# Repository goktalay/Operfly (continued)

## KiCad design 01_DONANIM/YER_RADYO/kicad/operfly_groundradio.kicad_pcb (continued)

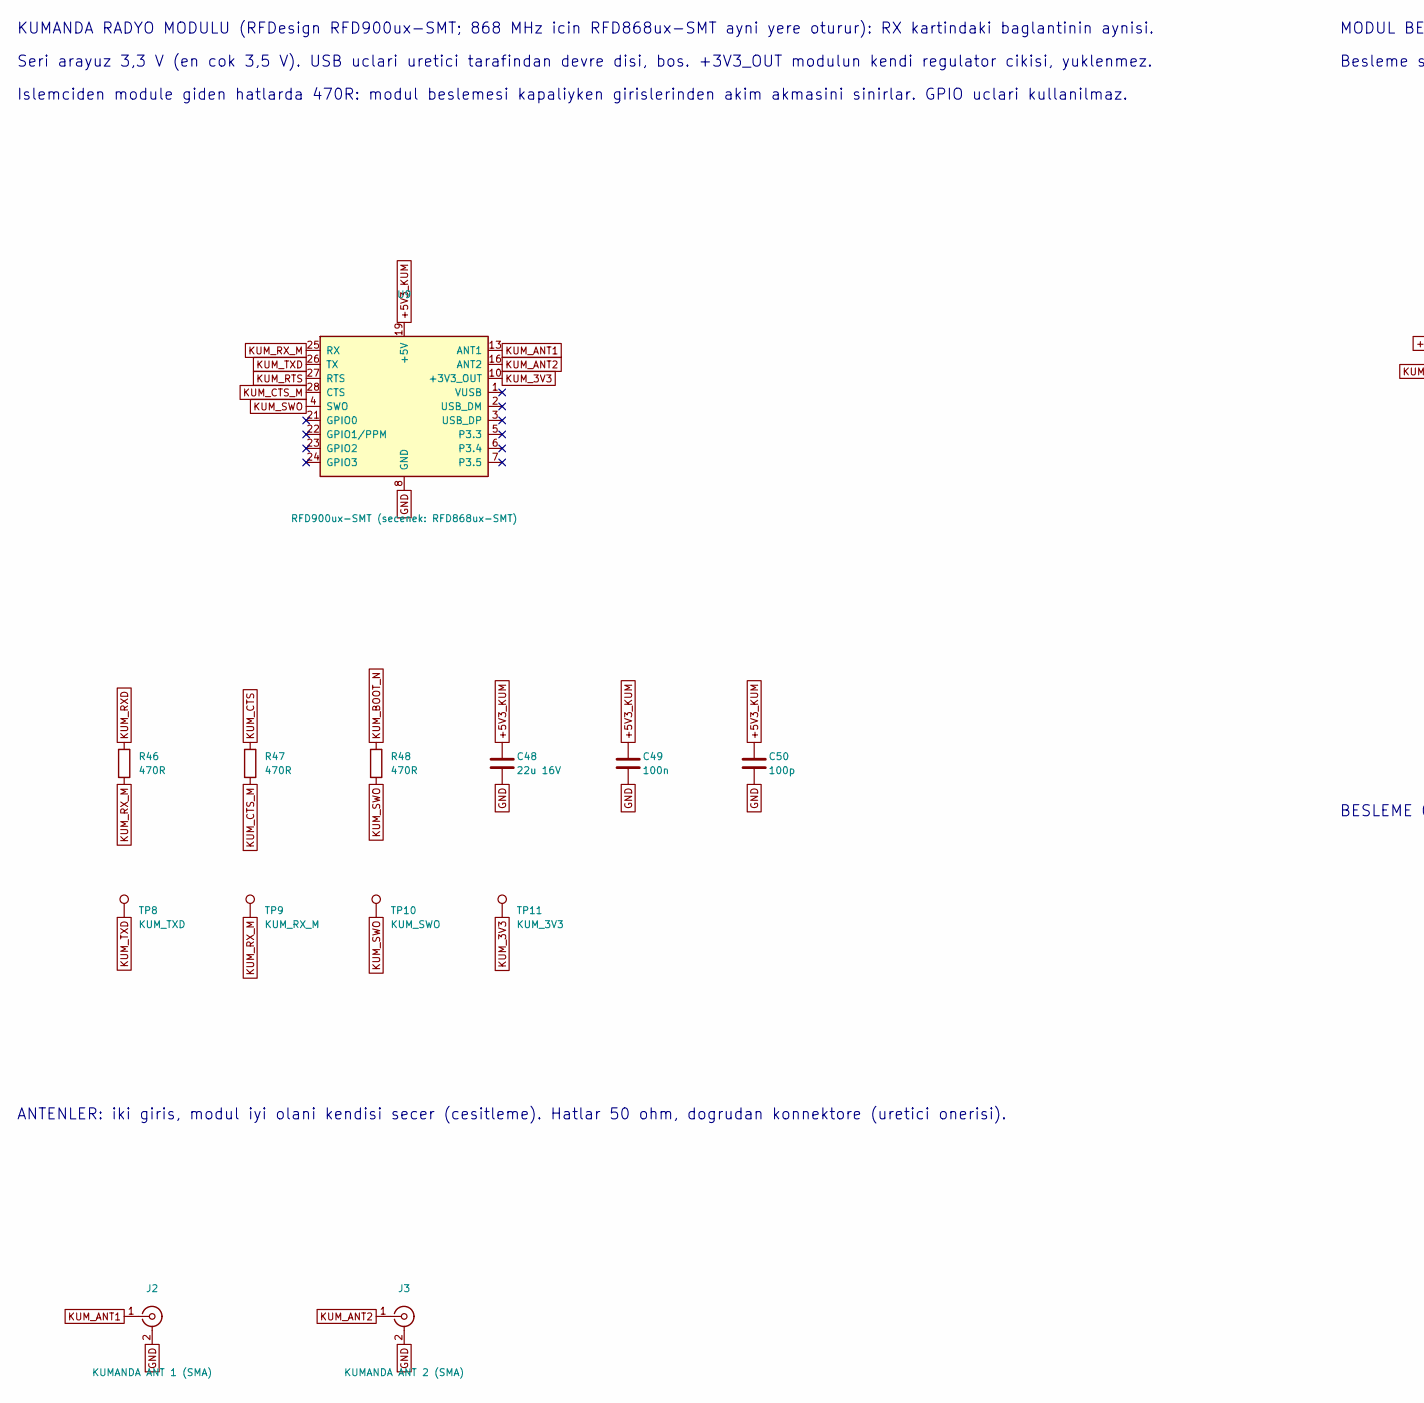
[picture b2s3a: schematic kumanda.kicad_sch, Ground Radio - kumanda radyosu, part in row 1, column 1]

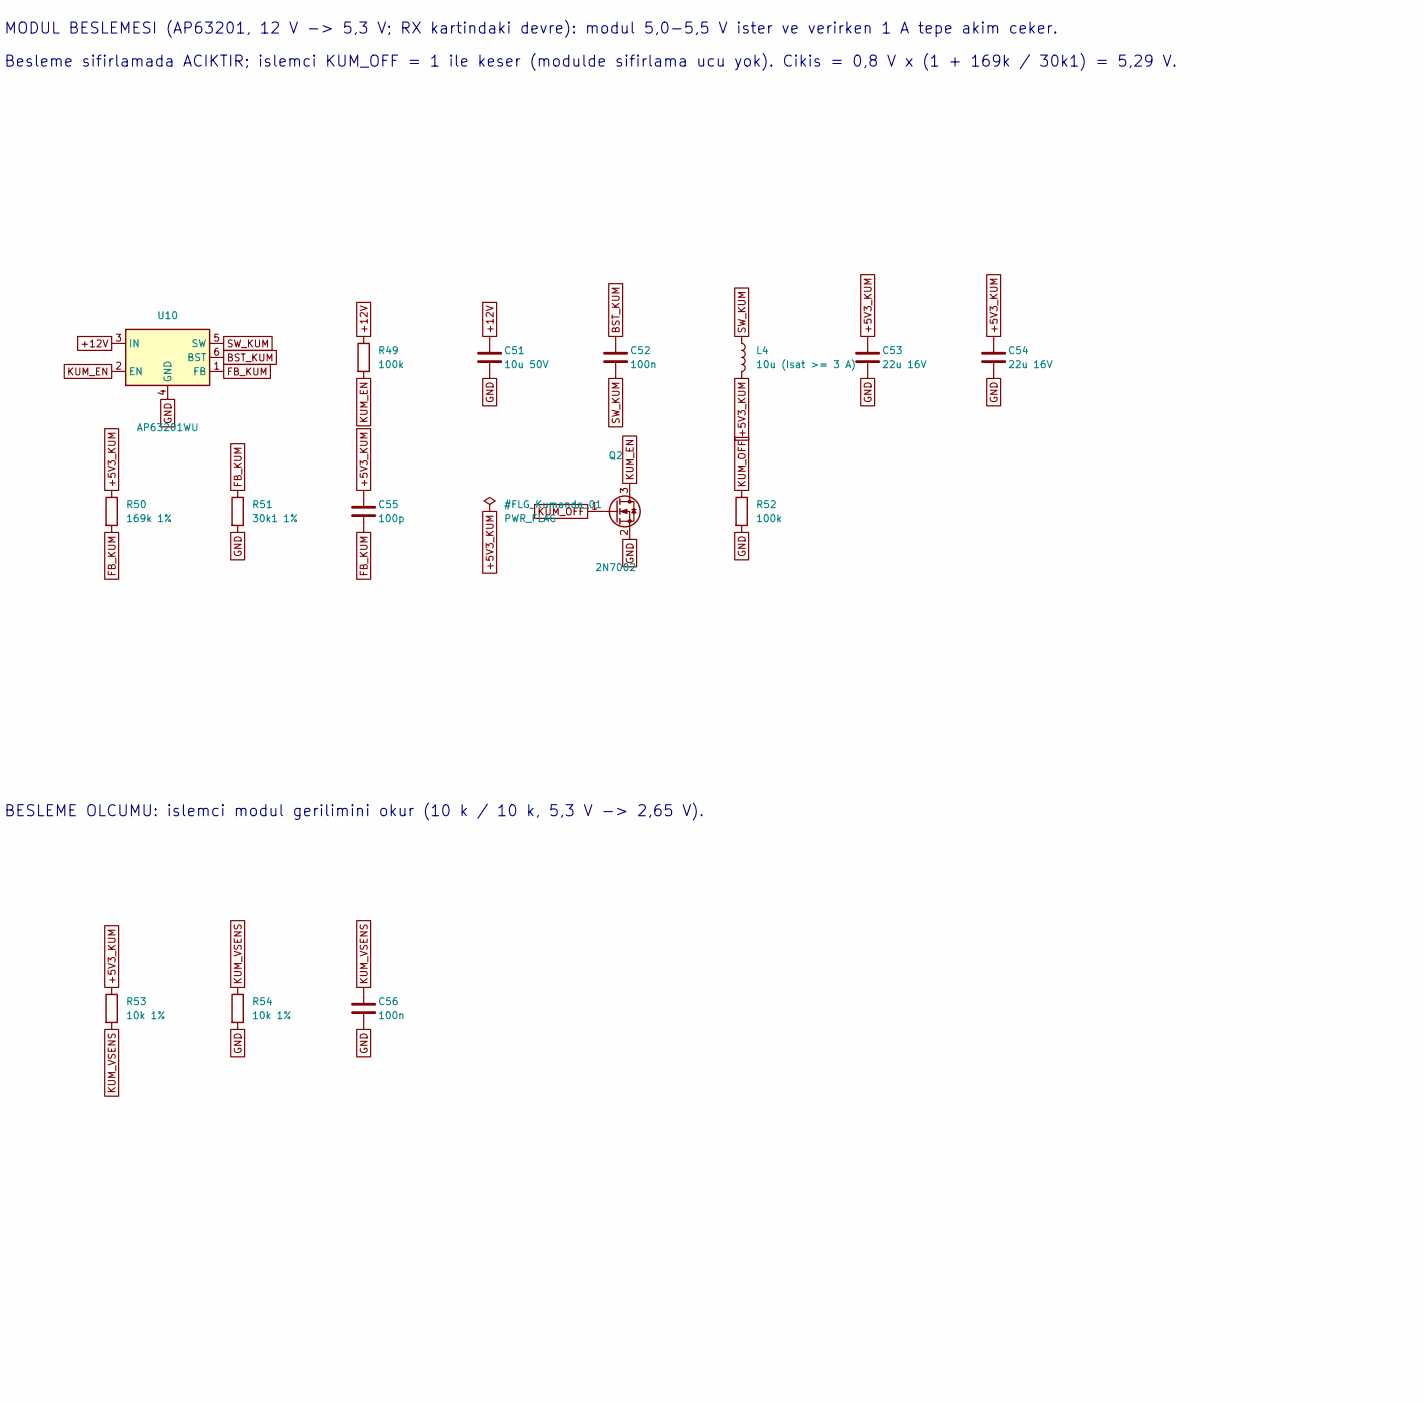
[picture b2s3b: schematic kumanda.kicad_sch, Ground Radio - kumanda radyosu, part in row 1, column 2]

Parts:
C48, C53, C54: 22u 16V; C_1206_3216Metric
C49, C52, C56: 100n; C_0402_1005Metric
C50, C55: 100p; C_0402_1005Metric
C51: 10u 50V; C_1206_3216Metric
J2: KUMANDA ANT 1 (SMA); SMA_Amphenol_132289_EdgeMount
J3: KUMANDA ANT 2 (SMA); SMA_Amphenol_132289_EdgeMount
L4: 10u (Isat >= 3 A); L_Coilcraft_XAL5030-XXX
Q2: 2N7002; SOT-23
R46, R47, R48: 470R; R_0402_1005Metric
R49, R52: 100k; R_0402_1005Metric
R50: 169k 1%; R_0402_1005Metric
R51: 30k1 1%; R_0402_1005Metric
R53, R54: 10k 1%; R_0402_1005Metric
TP8: KUM_TXD; TestPoint_Pad_D1.0mm
TP9: KUM_RX_M; TestPoint_Pad_D1.0mm
TP10: KUM_SWO; TestPoint_Pad_D1.0mm
TP11: KUM_3V3; TestPoint_Pad_D1.0mm
U9: RFD900ux-SMT (secenek: RFD868ux-SMT); RFDesign_RFD900ux-SMT
U10: AP63201WU; TSOT-23-6

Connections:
+5V3_KUM: C48.1, C49.1, C50.1, C53.1, C54.1, C55.1, L4.2, R50.1, R53.1, U9.19 (+5V)
+12V: C51.1, R49.1, U10.3 (IN); also elsewhere on the board
BST_KUM: C52.1, U10.6 (BST)
FB_KUM: C55.2, R50.2, R51.1, U10.1 (FB)
GND: C48.2, C49.2, C50.2, C51.2, C53.2, C54.2, C56.2, J2.2 (Ext), J3.2 (Ext), Q2.2 (S), R51.2, R52.2, R54.2, U9.8 (GND), U9.9 (GND), U9.11 (GND), U9.12 (GND), U9.14 (GND), U9.15 (GND), U9.17 (GND), U9.18 (GND), U9.20 (GND), U9.29 (GND), U9.30 (GND), U10.4 (GND); also elsewhere on the board
KUM_3V3: TP11.1, U9.10 (+3V3_OUT)
KUM_ANT1: J2.1 (In), U9.13 (ANT1)
KUM_ANT2: J3.1 (In), U9.16 (ANT2)
KUM_BOOT_N: R48.1; also elsewhere on the board
KUM_CTS: R47.1; also elsewhere on the board
KUM_CTS_M: R47.2, U9.28 (CTS)
KUM_EN: Q2.3 (D), R49.2, U10.2 (EN)
KUM_OFF: Q2.1 (G), R52.1; also elsewhere on the board
KUM_RTS: U9.27 (RTS); also elsewhere on the board
KUM_RXD: R46.1; also elsewhere on the board
KUM_RX_M: R46.2, TP9.1, U9.25 (RX)
KUM_SWO: R48.2, TP10.1, U9.4 (SWO)
KUM_TXD: TP8.1, U9.26 (TX); also elsewhere on the board
KUM_VSENS: C56.1, R53.2, R54.1; also elsewhere on the board
SW_KUM: C52.2, L4.1, U10.5 (SW)

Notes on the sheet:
Islemciden module giden hatlarda 470R: modul beslemesi kapaliyken girislerinden akim akmasini sinirlar. GPIO uclari kullanilmaz.
BESLEME OLCUMU: islemci modul gerilimini okur (10 k / 10 k, 5,3 V -> 2,65 V).
Seri arayuz 3,3 V (en cok 3,5 V). USB uclari uretici tarafindan devre disi, bos. +3V3_OUT modulun kendi regulator cikisi, yuklenmez.
MODUL BESLEMESI (AP63201, 12 V -> 5,3 V; RX kartindaki devre): modul 5,0-5,5 V ister ve verirken 1 A tepe akim ceker.
Besleme sifirlamada ACIKTIR; islemci KUM_OFF = 1 ile keser (modulde sifirlama ucu yok). Cikis = 0,8 V x (1 + 169k / 30k1) = 5,29 V.
ANTENLER: iki giris, modul iyi olani kendisi secer (cesitleme). Hatlar 50 ohm, dogrudan konnektore (uretici onerisi).
KUMANDA RADYO MODULU (RFDesign RFD900ux-SMT; 868 MHz icin RFD868ux-SMT ayni yere oturur): RX kartindaki baglantinin aynisi.

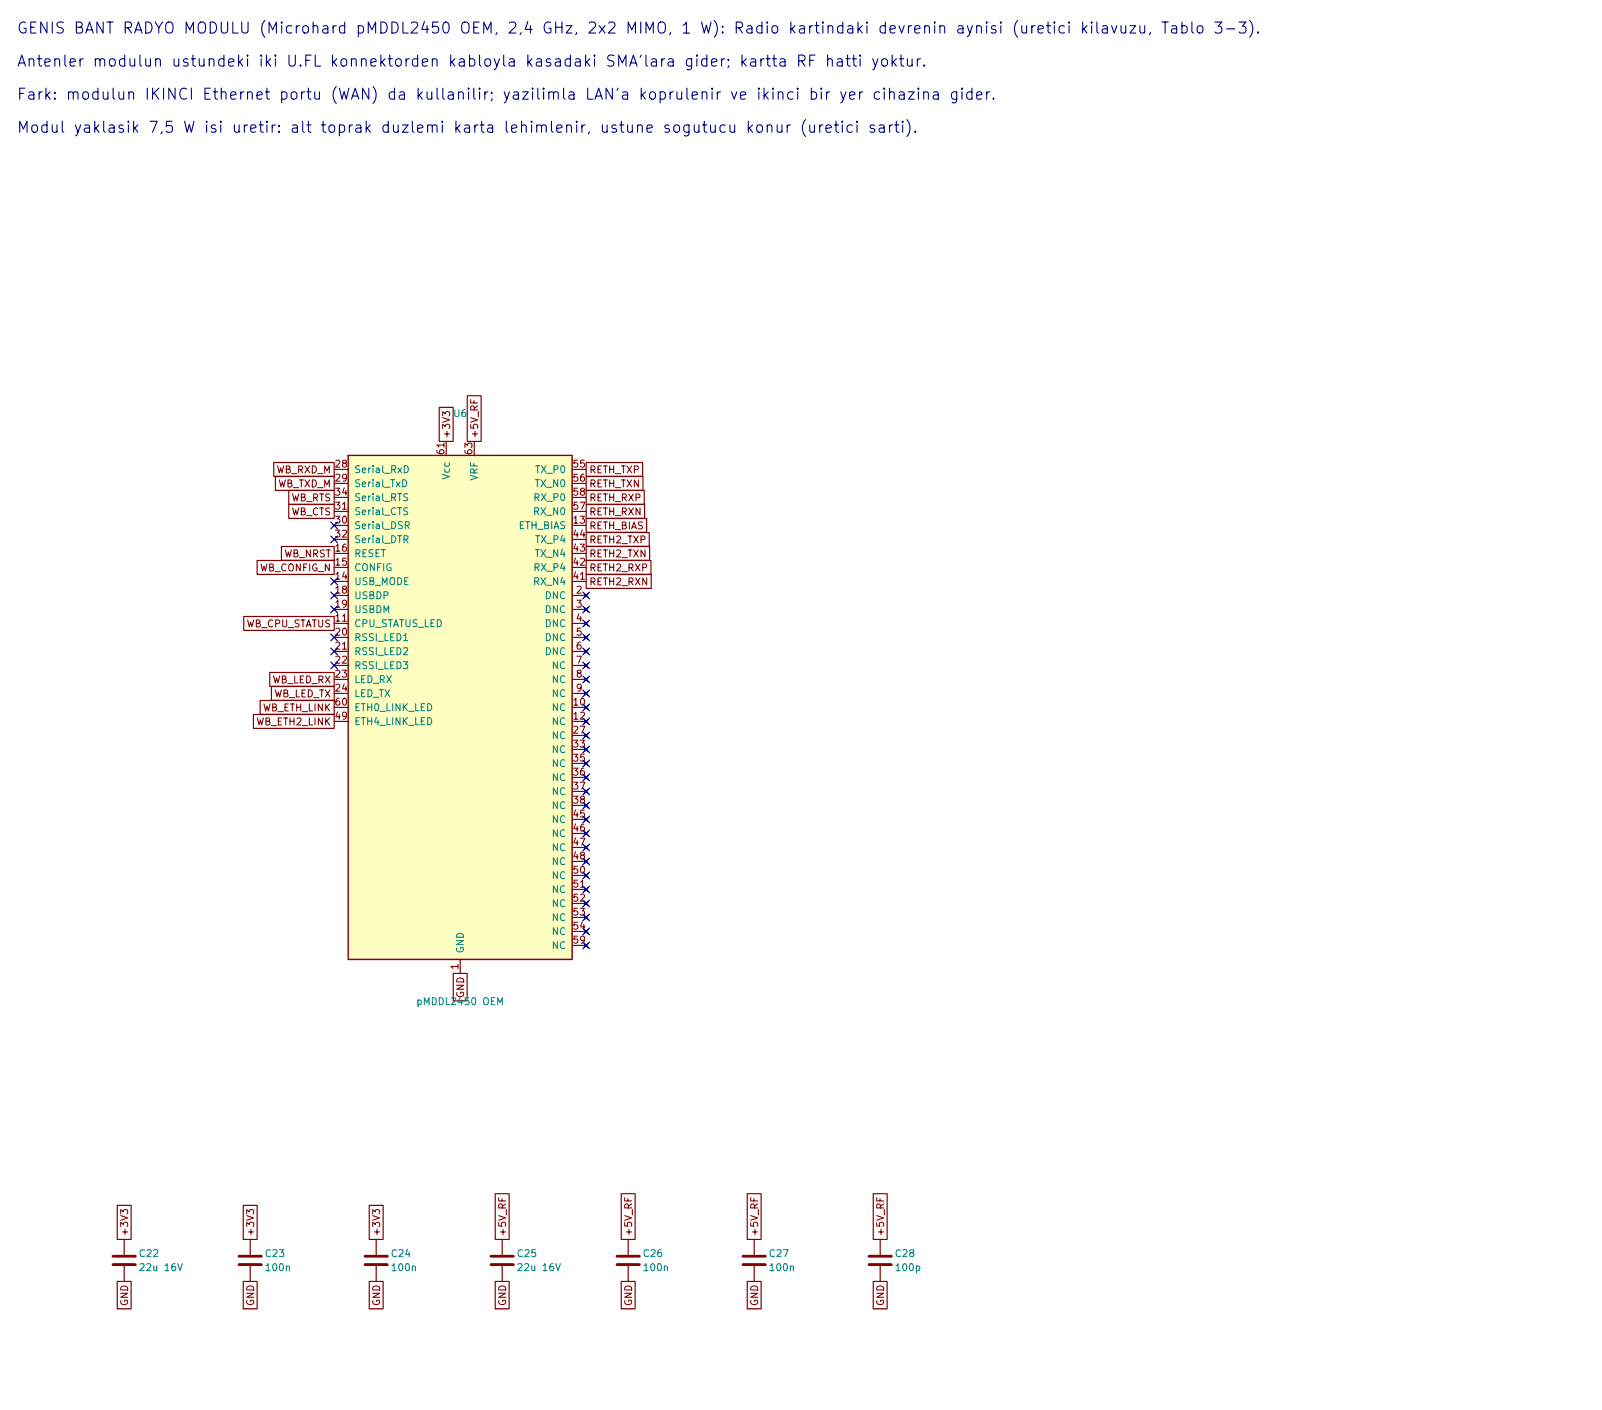
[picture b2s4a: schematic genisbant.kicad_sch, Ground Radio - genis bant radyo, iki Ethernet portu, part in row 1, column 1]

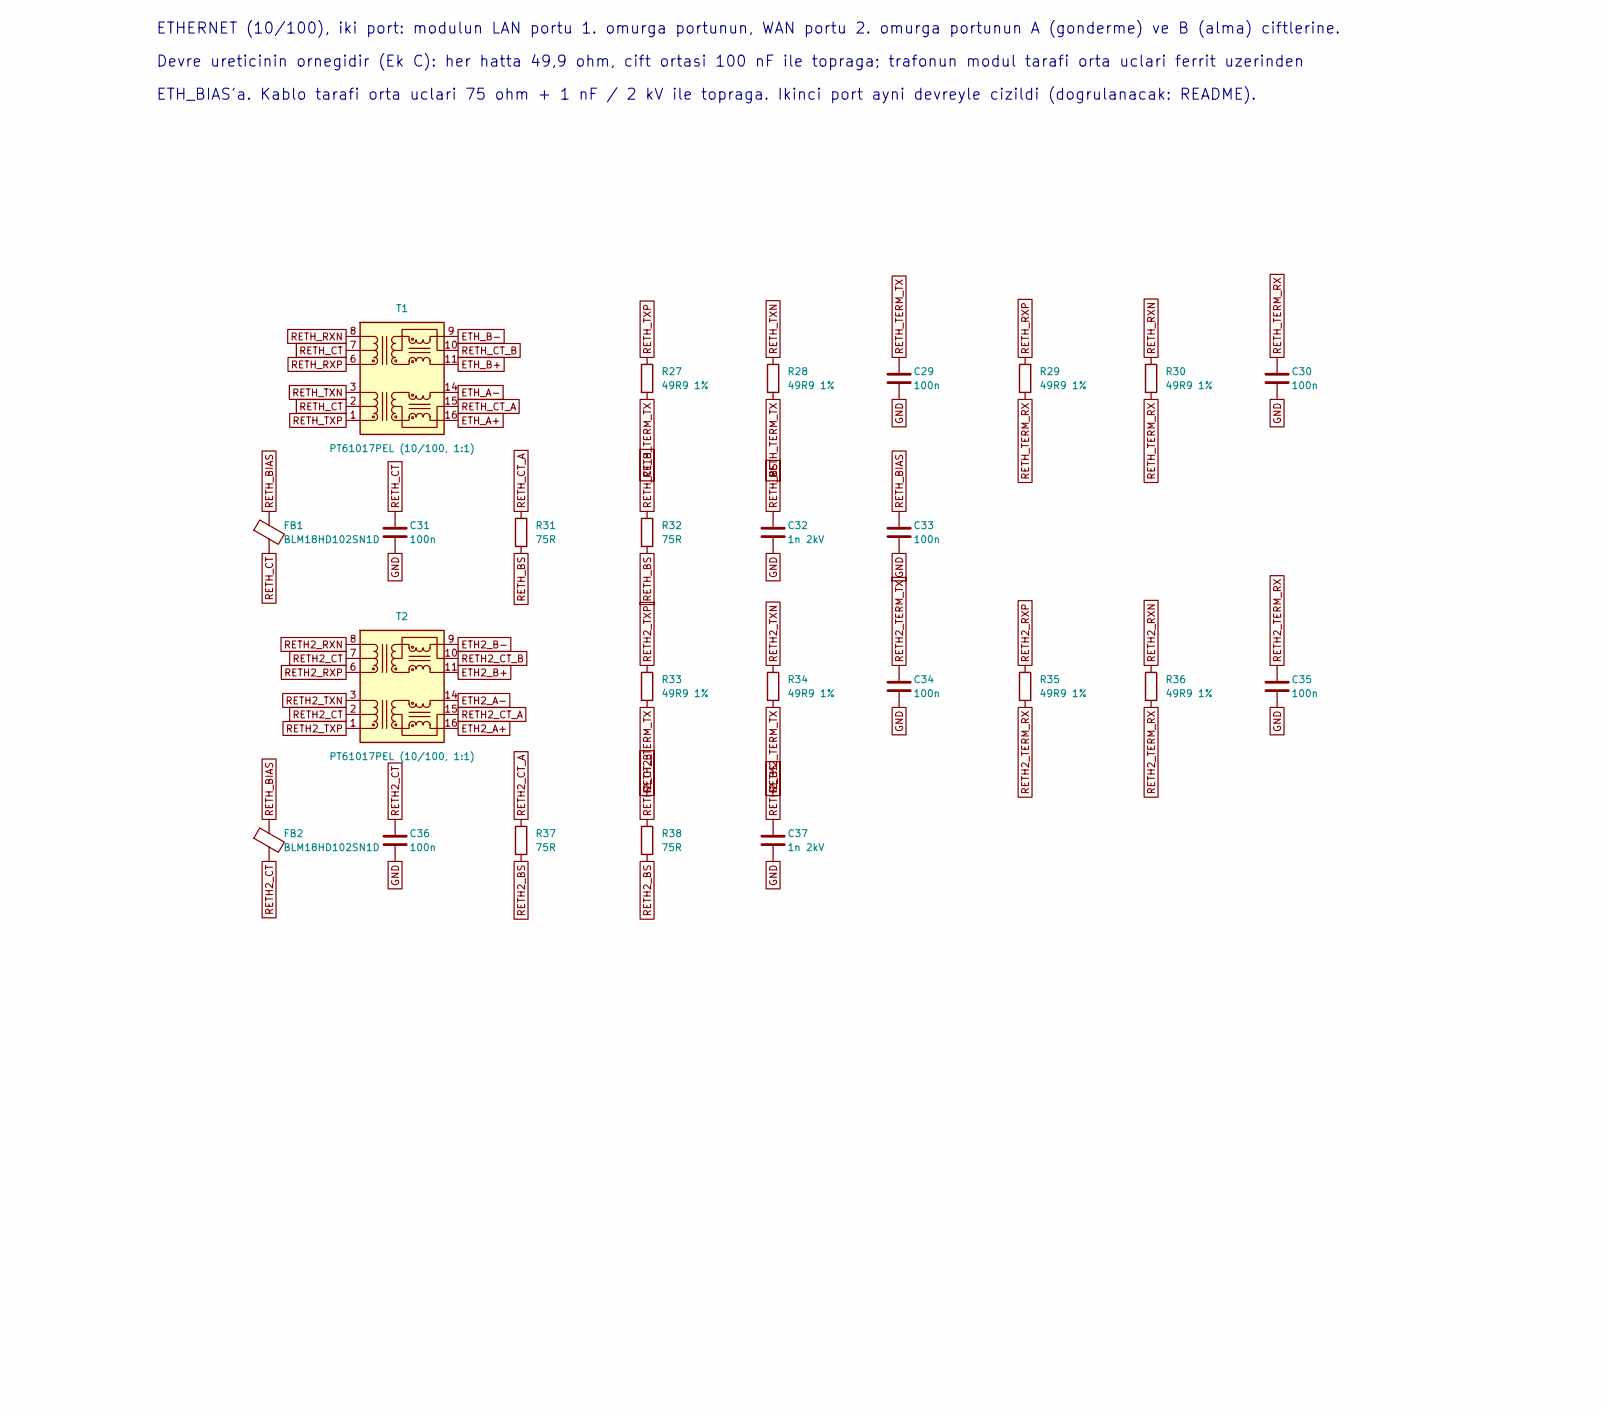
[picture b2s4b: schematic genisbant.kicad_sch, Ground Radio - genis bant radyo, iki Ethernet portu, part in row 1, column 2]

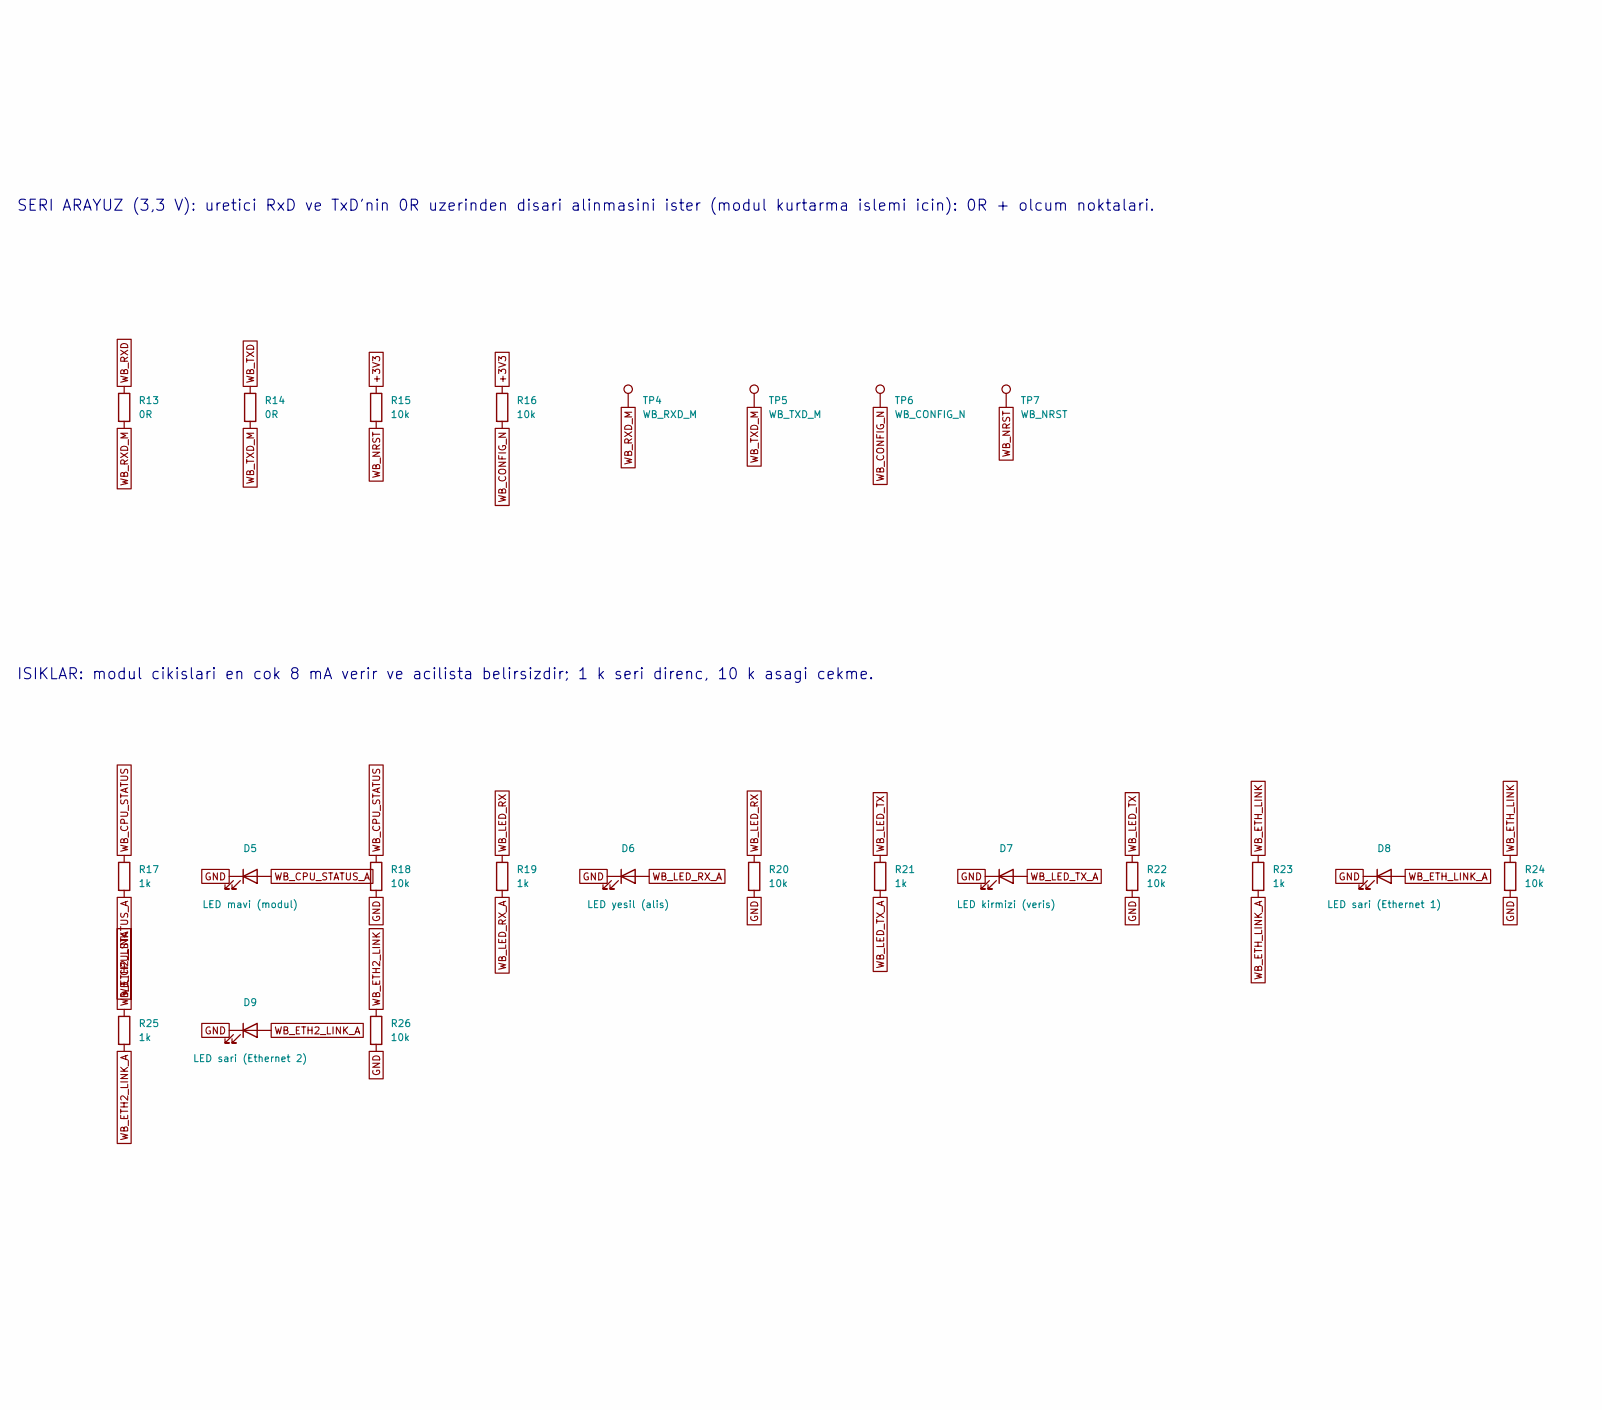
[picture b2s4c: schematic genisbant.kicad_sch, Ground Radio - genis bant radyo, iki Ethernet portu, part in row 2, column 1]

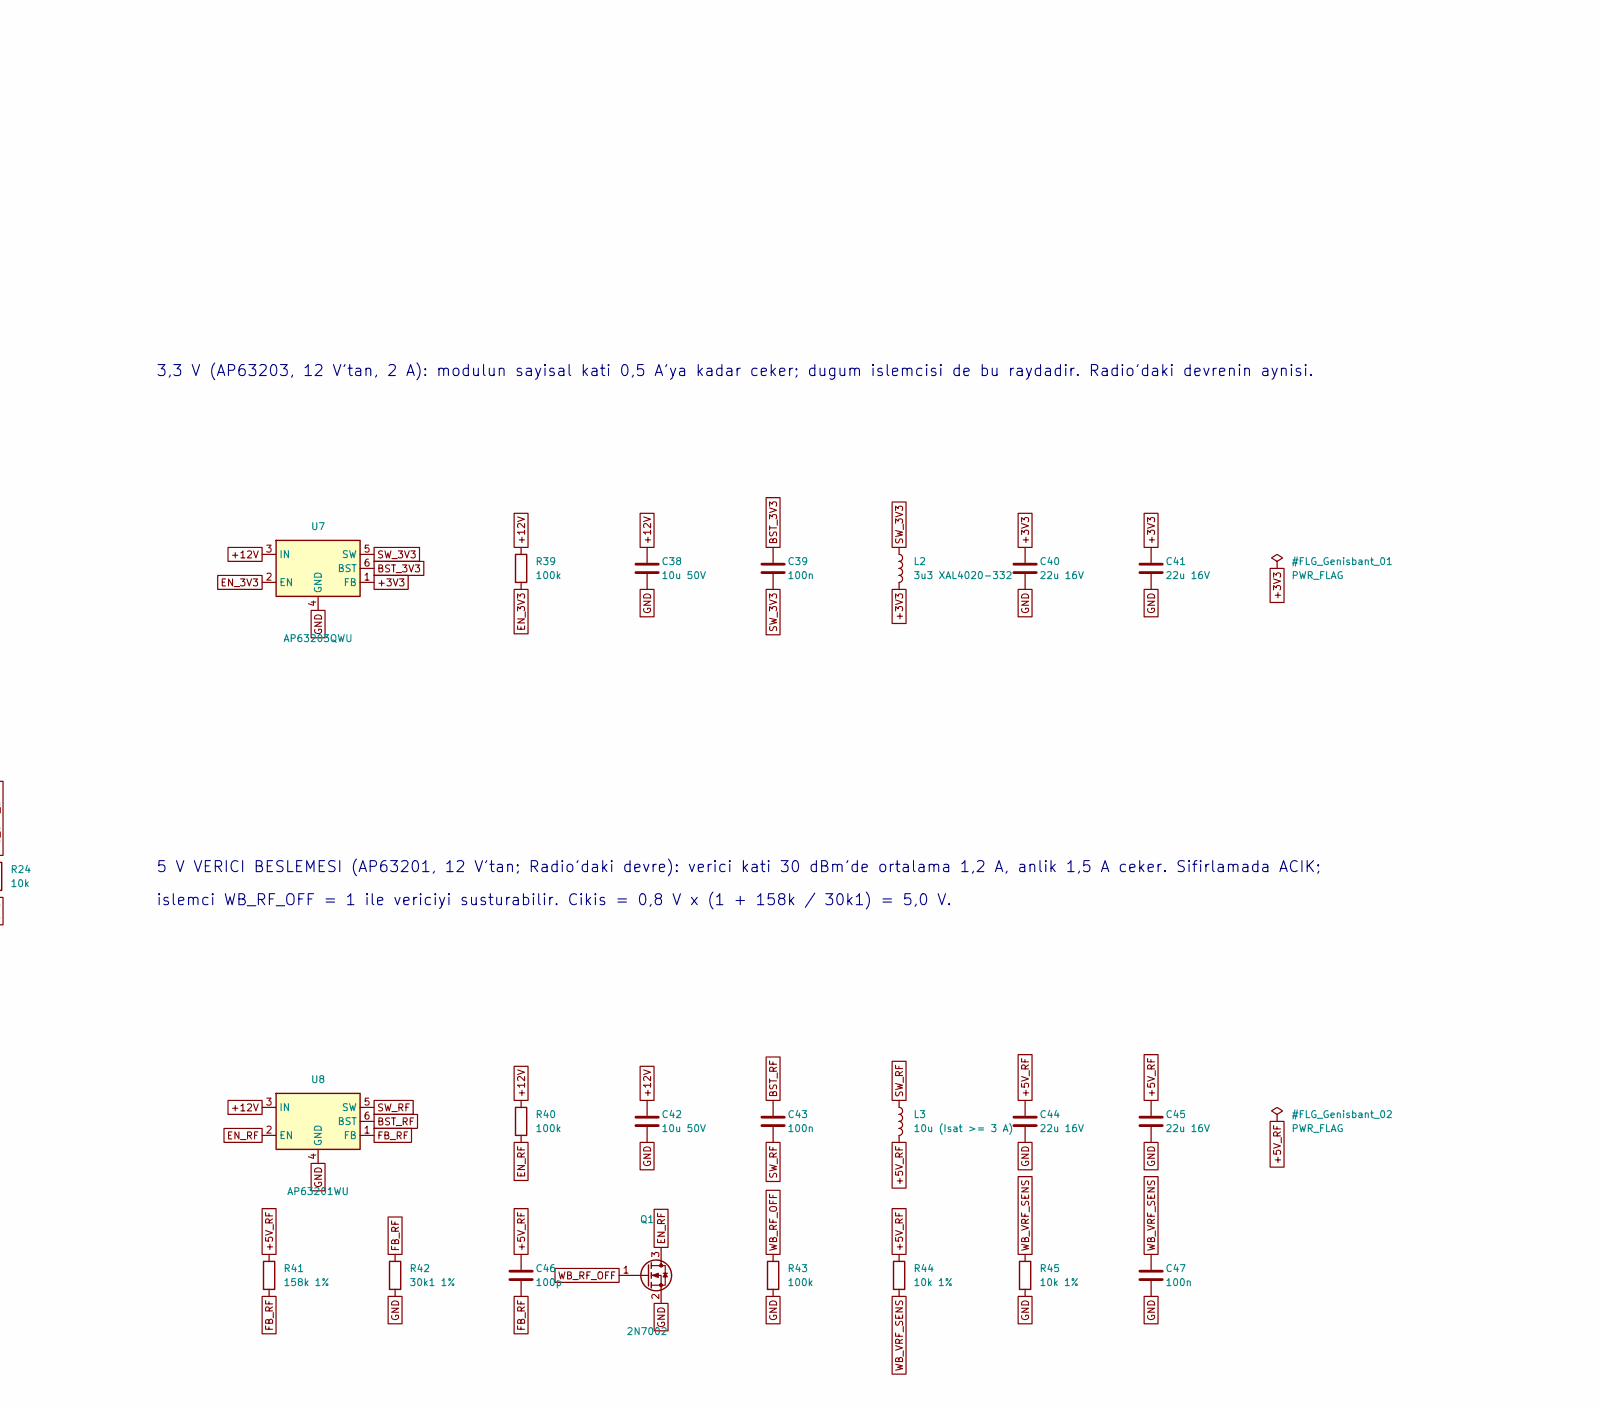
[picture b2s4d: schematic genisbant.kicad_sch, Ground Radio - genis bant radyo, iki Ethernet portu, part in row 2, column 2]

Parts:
C22, C25, C40, C41, C44, C45: 22u 16V; C_1206_3216Metric
C23, C24, C26, C27, C29, C30, C31, C33, C34, C35, C36, C39, C43, C47: 100n; C_0402_1005Metric
C28, C46: 100p; C_0402_1005Metric
C32, C37: 1n 2kV; C_1206_3216Metric
C38, C42: 10u 50V; C_1206_3216Metric
D5: LED mavi (modul); LED_0603_1608Metric
D6: LED yesil (alis); LED_0603_1608Metric
D7: LED kirmizi (veris); LED_0603_1608Metric
D8: LED sari (Ethernet 1); LED_0603_1608Metric
D9: LED sari (Ethernet 2); LED_0603_1608Metric
FB1, FB2: BLM18HD102SN1D; L_0603_1608Metric
L2: 3u3 XAL4020-332; L_Coilcraft_XAL4020-XXX
L3: 10u (Isat >= 3 A); L_Coilcraft_XAL5030-XXX
Q1: 2N7002; SOT-23
R13, R14: 0R; R_0402_1005Metric
R15, R16, R18, R20, R22, R24, R26: 10k; R_0402_1005Metric
R17, R19, R21, R23, R25: 1k; R_0402_1005Metric
R27, R28, R29, R30, R33, R34, R35, R36: 49R9 1%; R_0402_1005Metric
R31, R32, R37, R38: 75R; R_0402_1005Metric
R39, R40, R43: 100k; R_0402_1005Metric
R41: 158k 1%; R_0402_1005Metric
R42: 30k1 1%; R_0402_1005Metric
R44, R45: 10k 1%; R_0402_1005Metric
T1, T2: PT61017PEL (10/100, 1:1); Transformer_Ethernet_Bourns_PT61017PEL
TP4: WB_RXD_M; TestPoint_Pad_D1.0mm
TP5: WB_TXD_M; TestPoint_Pad_D1.0mm
TP6: WB_CONFIG_N; TestPoint_Pad_D1.0mm
TP7: WB_NRST; TestPoint_Pad_D1.0mm
U6: pMDDL2450 OEM; Microhard_pMDDL_OEM
U7: AP63203QWU; TSOT-23-6
U8: AP63201WU; TSOT-23-6

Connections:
+3V3: C22.1, C23.1, C24.1, C40.1, C41.1, L2.2, R15.1, R16.1, U6.61 (Vcc), U6.62 (Vcc), U7.1 (FB); also elsewhere on the board
+5V_RF: C25.1, C26.1, C27.1, C28.1, C44.1, C45.1, C46.1, L3.2, R41.1, R44.1, U6.63 (VRF), U6.64 (VRF)
+12V: C38.1, C42.1, R39.1, R40.1, U7.3 (IN), U8.3 (IN); also elsewhere on the board
BST_3V3: C39.1, U7.6 (BST)
BST_RF: C43.1, U8.6 (BST)
EN_3V3: R39.2, U7.2 (EN)
EN_RF: Q1.3 (D), R40.2, U8.2 (EN)
ETH2_A+: T2.16 (TX+); also elsewhere on the board
ETH2_A-: T2.14 (TX-); also elsewhere on the board
ETH2_B+: T2.11 (RX+); also elsewhere on the board
ETH2_B-: T2.9 (RX-); also elsewhere on the board
ETH_A+: T1.16 (TX+); also elsewhere on the board
ETH_A-: T1.14 (TX-); also elsewhere on the board
ETH_B+: T1.11 (RX+); also elsewhere on the board
ETH_B-: T1.9 (RX-); also elsewhere on the board
FB_RF: C46.2, R41.2, R42.1, U8.1 (FB)
GND: C22.2, C23.2, C24.2, C25.2, C26.2, C27.2, C28.2, C29.2, C30.2, C31.2, C32.2, C33.2, C34.2, C35.2, C36.2, C37.2, C38.2, C40.2, C41.2, C42.2, C44.2, C45.2, C47.2, D5.1 (K), D6.1 (K), D7.1 (K), D8.1 (K), D9.1 (K), Q1.2 (S), R18.2, R20.2, R22.2, R24.2, R26.2, R42.2, R43.2, R45.2, U6.1 (GND), U6.17 (GND), U6.25 (GND), U6.26 (GND), U6.39 (GND), U6.40 (GND), U6.65 (GND), U6.66 (GND), U6.67 (GND), U6.68 (GND), U6.69 (GND), U6.70 (GND), U6.71 (GND), U6.72 (GND), U6.73 (GND), U6.74 (GND), U6.75 (GND), U6.76 (GND), U6.77 (GND), U6.78 (GND), U6.79 (GND), U6.80 (GND), U6.81 (GND), U7.4 (GND), U8.4 (GND); also elsewhere on the board
RETH2_BS: C37.1, R37.2, R38.2
RETH2_CT: C36.1, FB2.2, T2.2 (C_TD), T2.7 (C_RD)
RETH2_CT_A: R37.1, T2.15 (C_TX)
RETH2_CT_B: R38.1, T2.10 (C_RX)
RETH2_RXN: R36.1, T2.8 (RD-), U6.41 (RX_N4)
RETH2_RXP: R35.1, T2.6 (RD+), U6.42 (RX_P4)
RETH2_TERM_RX: C35.1, R35.2, R36.2
RETH2_TERM_TX: C34.1, R33.2, R34.2
RETH2_TXN: R34.1, T2.3 (TD-), U6.43 (TX_N4)
RETH2_TXP: R33.1, T2.1 (TD+), U6.44 (TX_P4)
RETH_BIAS: C33.1, FB1.1, FB2.1, U6.13 (ETH_BIAS)
RETH_BS: C32.1, R31.2, R32.2
RETH_CT: C31.1, FB1.2, T1.2 (C_TD), T1.7 (C_RD)
RETH_CT_A: R31.1, T1.15 (C_TX)
RETH_CT_B: R32.1, T1.10 (C_RX)
RETH_RXN: R30.1, T1.8 (RD-), U6.57 (RX_N0)
RETH_RXP: R29.1, T1.6 (RD+), U6.58 (RX_P0)
RETH_TERM_RX: C30.1, R29.2, R30.2
RETH_TERM_TX: C29.1, R27.2, R28.2
RETH_TXN: R28.1, T1.3 (TD-), U6.56 (TX_N0)
RETH_TXP: R27.1, T1.1 (TD+), U6.55 (TX_P0)
SW_3V3: C39.2, L2.1, U7.5 (SW)
SW_RF: C43.2, L3.1, U8.5 (SW)
WB_CONFIG_N: R16.2, TP6.1, U6.15 (CONFIG); also elsewhere on the board
WB_CPU_STATUS: R17.1, R18.1, U6.11 (CPU_STATUS_LED); also elsewhere on the board
WB_CPU_STATUS_A: D5.2 (A), R17.2
WB_CTS: U6.31 (Serial_CTS); also elsewhere on the board
WB_ETH2_LINK: R25.1, R26.1, U6.49 (ETH4_LINK_LED)
WB_ETH2_LINK_A: D9.2 (A), R25.2
WB_ETH_LINK: R23.1, R24.1, U6.60 (ETH0_LINK_LED)
WB_ETH_LINK_A: D8.2 (A), R23.2
WB_LED_RX: R19.1, R20.1, U6.23 (LED_RX)
WB_LED_RX_A: D6.2 (A), R19.2
WB_LED_TX: R21.1, R22.1, U6.24 (LED_TX)
WB_LED_TX_A: D7.2 (A), R21.2
WB_NRST: R15.2, TP7.1, U6.16 (RESET); also elsewhere on the board
WB_RF_OFF: Q1.1 (G), R43.1; also elsewhere on the board
WB_RTS: U6.34 (Serial_RTS); also elsewhere on the board
WB_RXD: R13.1; also elsewhere on the board
WB_RXD_M: R13.2, TP4.1, U6.28 (Serial_RxD)
WB_TXD: R14.1; also elsewhere on the board
WB_TXD_M: R14.2, TP5.1, U6.29 (Serial_TxD)
WB_VRF_SENS: C47.1, R44.2, R45.1; also elsewhere on the board

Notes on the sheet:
Modul yaklasik 7,5 W isi uretir: alt toprak duzlemi karta lehimlenir, ustune sogutucu konur (uretici sarti).
Fark: modulun IKINCI Ethernet portu (WAN) da kullanilir; yazilimla LAN'a koprulenir ve ikinci bir yer cihazina gider.
ETHERNET (10/100), iki port: modulun LAN portu 1. omurga portunun, WAN portu 2. omurga portunun A (gonderme) ve B (alma) ciftlerine.
3,3 V (AP63203, 12 V'tan, 2 A): modulun sayisal kati 0,5 A'ya kadar ceker; dugum islemcisi de bu raydadir. Radio'daki devrenin aynisi.
ETH_BIAS'a. Kablo tarafi orta uclari 75 ohm + 1 nF / 2 kV ile topraga. Ikinci port ayni devreyle cizildi (dogrulanacak: README).
islemci WB_RF_OFF = 1 ile vericiyi susturabilir. Cikis = 0,8 V x (1 + 158k / 30k1) = 5,0 V.
ISIKLAR: modul cikislari en cok 8 mA verir ve acilista belirsizdir; 1 k seri direnc, 10 k asagi cekme.
SERI ARAYUZ (3,3 V): uretici RxD ve TxD'nin 0R uzerinden disari alinmasini ister (modul kurtarma islemi icin): 0R + olcum noktalari.
Antenler modulun ustundeki iki U.FL konnektorden kabloyla kasadaki SMA'lara gider; kartta RF hatti yoktur.
GENIS BANT RADYO MODULU (Microhard pMDDL2450 OEM, 2,4 GHz, 2x2 MIMO, 1 W): Radio kartindaki devrenin aynisi (uretici kilavuzu, Tablo 3-3).
Devre ureticinin ornegidir (Ek C): her hatta 49,9 ohm, cift ortasi 100 nF ile topraga; trafonun modul tarafi orta uclari ferrit uzerinden
5 V VERICI BESLEMESI (AP63201, 12 V'tan; Radio'daki devre): verici kati 30 dBm'de ortalama 1,2 A, anlik 1,5 A ceker. Sifirlamada ACIK;
